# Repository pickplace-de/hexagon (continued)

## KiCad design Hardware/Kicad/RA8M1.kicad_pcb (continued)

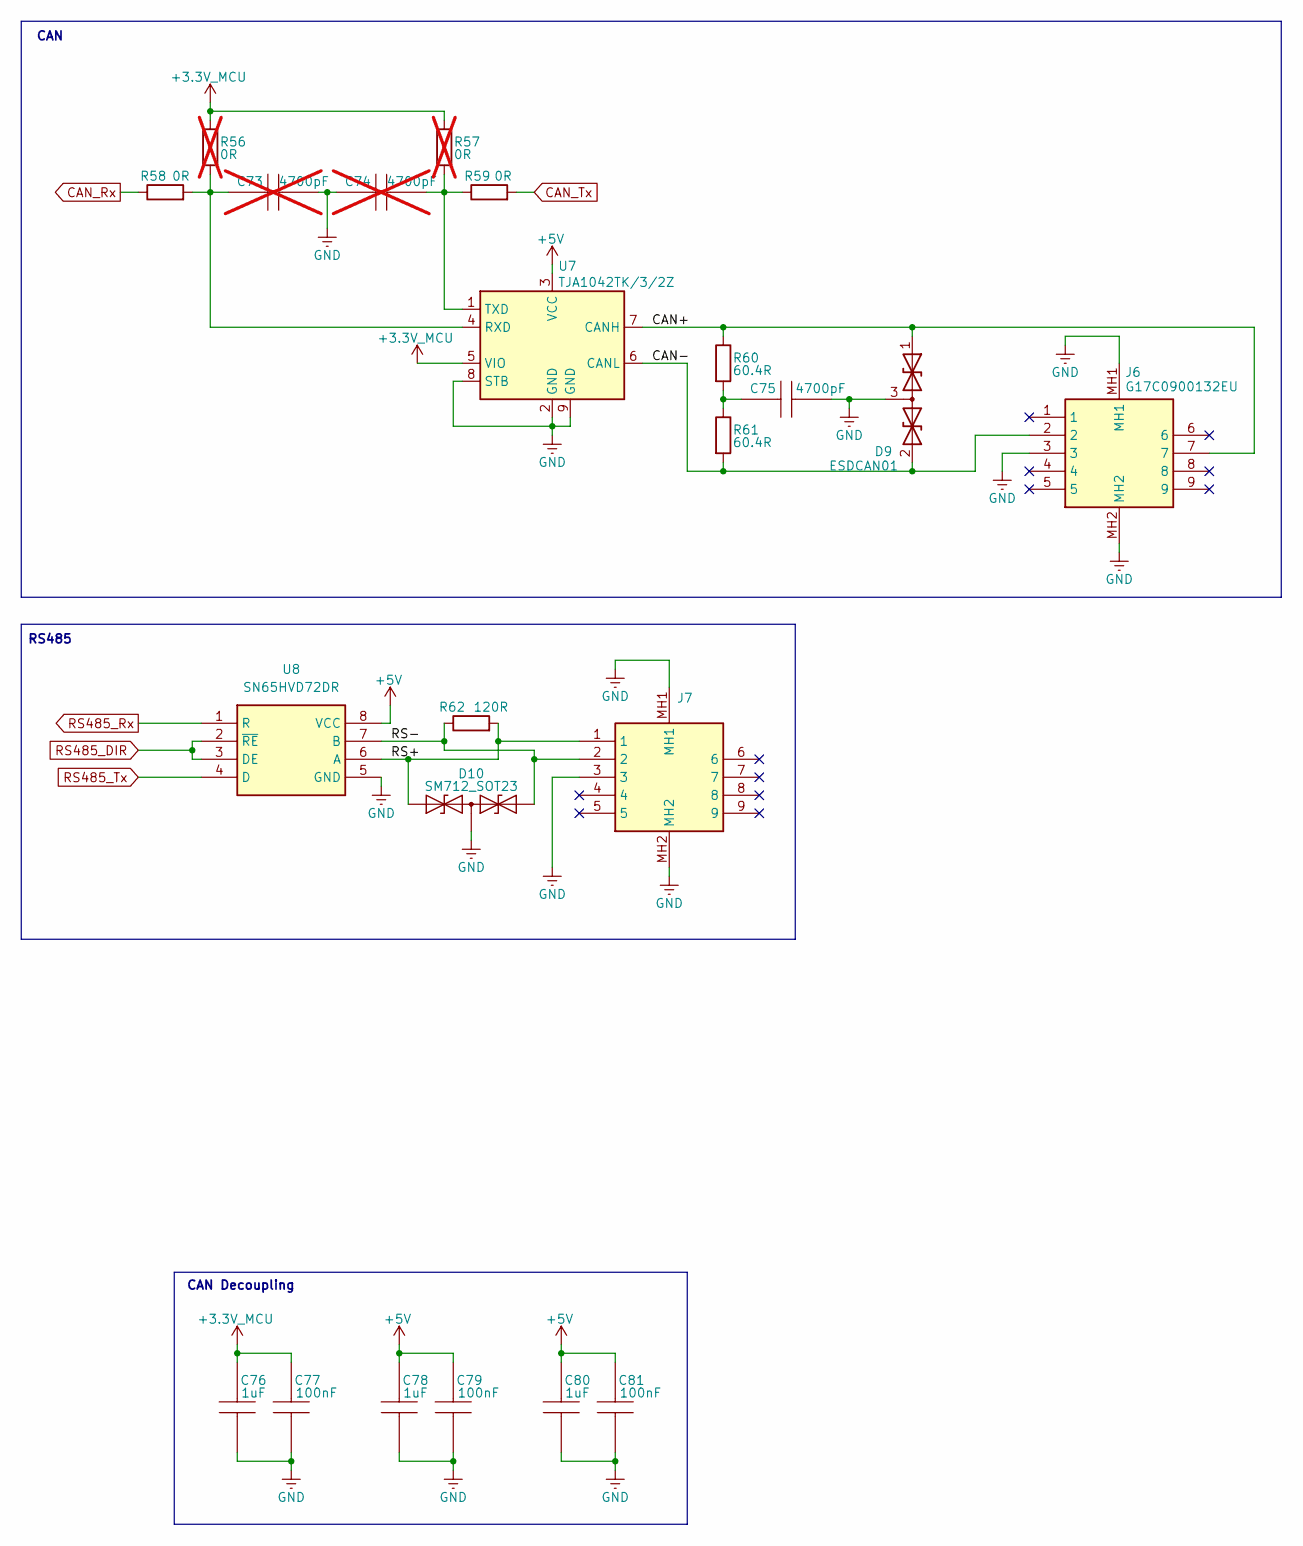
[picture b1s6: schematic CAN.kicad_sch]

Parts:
C73, C74: 4700pF; C_0603_1608Metric; MPN 885012104008; not fitted
C75: 4700pF; C_0603_1608Metric; MPN 885012104008
C76, C78, C80: 1uF; C_0402_1005Metric; MPN 885012105006
C77, C79, C81: 100nF; C_0402_1005Metric; MPN 885012205092
D9: ESDCAN01; TSOT-23
D10: SM712_SOT23; SOT-23
J6, J7: G17C0900132EU; Mouser Part Number 523-G17C0900132EU
R56, R57: 0R; R_0402_1005Metric; MPN 560112110001; not fitted
R58, R59: 0R; R_0402_1005Metric; MPN 560112110001
R60, R61: 60.4R; R_0402_1005Metric; MPN 560112110170
R62: 120R; R_0402_1005Metric; MPN 560112110001
U7: TJA1042TK/3/2Z; DFN-8-1EP_3x3mm_P0.65mm_EP1.55x2.4mm; MPN TJA1042TK/3/2Z
U8: SN65HVD72DR; SOIC127P600X175-8N; Mouser Part Number 595-SN65HVD72DR

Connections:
+3.3V_MCU: C76.2, C77.2, R56.1, R57.1, U7.5 (VIO); also elsewhere on the board
+5V: C78.2, C79.2, C80.2, C81.2, U7.3 (VCC), U8.8 (VCC); also elsewhere on the board
/CAN & RS485/CAN+: D9.1 (A1), J6.7, R60.1, U7.7 (CANH)
/CAN & RS485/CAN-: D9.2 (A2), J6.2, R61.2, U7.6 (CANL)
/CAN & RS485/RS+: D10.1 (A1), J7.1, R62.2, U8.6 (A)
/CAN & RS485/RS-: D10.2 (A2), J7.2, R62.1, U8.7 (B)
CAN_Rx: R58.1; also elsewhere on the board
CAN_Tx: R59.2; also elsewhere on the board
GND: C73.1, C74.2, C75.1, C76.1, C77.1, C78.1, C79.1, C80.1, C81.1, D9.3 (common), D10.3 (common), J6.3, J6.MH1, J6.MH2, J7.3, J7.MH1, J7.MH2, U7.2 (GND), U7.8 (STB), U7.9 (GND), U8.5 (GND); also elsewhere on the board
unnamed: C75.2, R60.2, R61.1
unnamed: C73.2, R56.2, R58.2, U7.4 (RXD)
unnamed: C74.1, R57.2, R59.1, U7.1 (TXD)
RS485_DIR: U8.2 (~RE), U8.3 (DE); also elsewhere on the board
RS485_Rx: U8.1 (R); also elsewhere on the board
RS485_Tx: U8.4 (D); also elsewhere on the board

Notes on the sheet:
CAN Decoupling
CAN
RS485

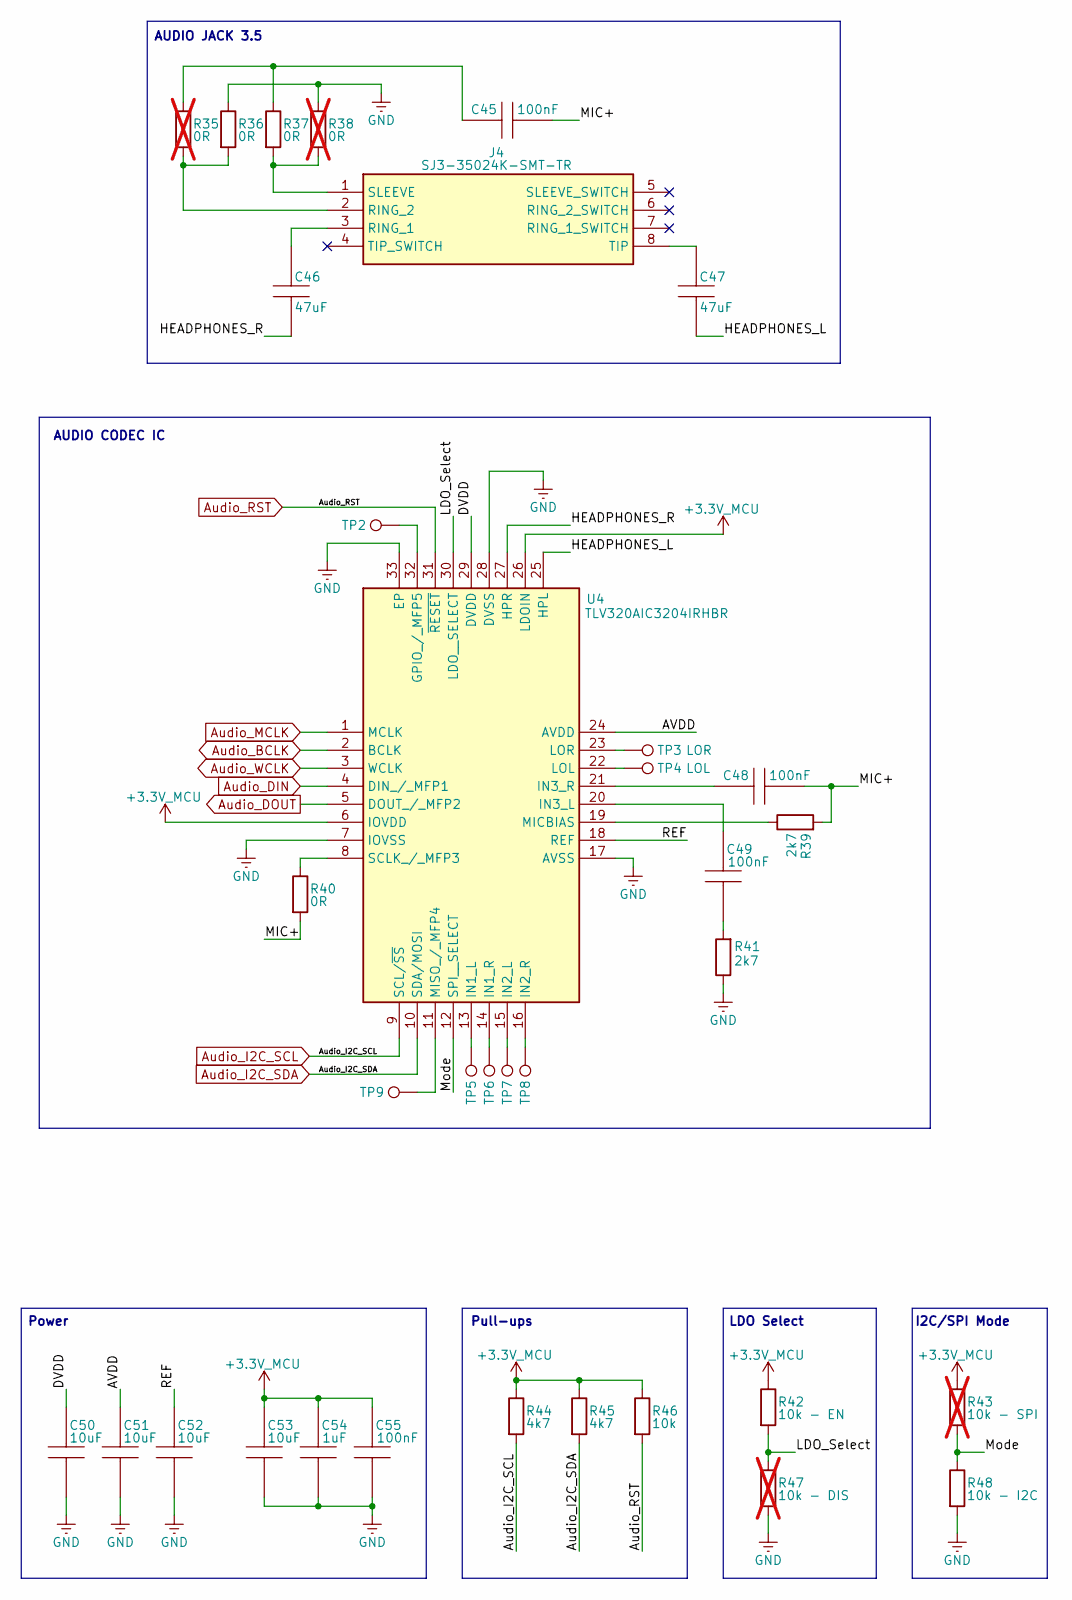
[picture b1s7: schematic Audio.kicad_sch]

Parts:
C45, C48, C49, C55: 100nF; C_0402_1005Metric; MPN 885012205092
C46, C47: 47uF; C_0805_2012Metric; MPN 885012107006
C50, C51, C52, C53: 10uF; C_0402_1005Metric; MPN 885012105020
C54: 1uF; C_0402_1005Metric; MPN 885012105006
J4: SJ3-35024K-SMT-TR; SJ335024KSMTTR; Mouser Part Number 179-SJ3-35024K-SMTTR
R35, R38: 0R; R_0402_1005Metric; MPN 560112110001; not fitted
R36, R37, R40: 0R; R_0402_1005Metric; MPN 560112110001
R39, R41: 2k7; R_0402_1005Metric; MPN 560112110266
R42: 10k - EN; R_0402_1005Metric; MPN 560112110020
R43: 10k - SPI; R_0402_1005Metric; MPN 560112110020; not fitted
R44, R45: 4k7; R_0402_1005Metric; MPN 560112110245
R46: 10k; R_0402_1005Metric; MPN 560112110020
R47: 10k - DIS; R_0402_1005Metric; MPN 560112110020; not fitted
R48: 10k - I2C; R_0402_1005Metric; MPN 560112110020
TP2, TP5, TP6, TP7, TP8, TP9: TestPoint_0.5mm
TP3: LOR; TestPoint_0.5mm
TP4: LOL; TestPoint_0.5mm
U4: TLV320AIC3204IRHBR; QFN50P500X500X100-33N-D; Mouser Part Number 595-V320AIC3204IRHBR

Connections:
+3.3V_MCU: C53.2, C54.2, C55.2, R42.1, R43.1, R44.1, R45.1, R46.1, U4.6 (IOVDD), U4.26 (LDOIN); also elsewhere on the board
/Audio/AVDD: C51.2, U4.24 (AVDD)
/Audio/DVDD: C50.2, U4.29 (DVDD)
/Audio/HEADPHONES_L: C47.2, U4.25 (HPL)
/Audio/HEADPHONES_R: C46.2, U4.27 (HPR)
/Audio/LDO_Select: R42.2, R47.1, U4.30 (LDO__SELECT)
/Audio/MIC+: C45.1, C48.1, R39.2, R40.2
/Audio/Mode: R43.2, R48.1, U4.12 (SPI__SELECT)
/Audio/REF: C52.2, U4.18 (REF)
Audio_BCLK: U4.2 (BCLK); also elsewhere on the board
Audio_DIN: U4.4 (DIN_/_MFP1); also elsewhere on the board
Audio_DOUT: U4.5 (DOUT_/_MFP2); also elsewhere on the board
Audio_I2C_SCL: R44.2, U4.9 (SCL/~SS); also elsewhere on the board
Audio_I2C_SDA: R45.2, U4.10 (SDA/MOSI); also elsewhere on the board
Audio_MCLK: U4.1 (MCLK); also elsewhere on the board
Audio_RST: R46.2, U4.31 (~RESET); also elsewhere on the board
Audio_WCLK: U4.3 (WCLK); also elsewhere on the board
GND: C50.1, C51.1, C52.1, C53.1, C54.1, C55.1, R36.1, R38.1, R41.1, R47.2, R48.2, U4.7 (IOVSS), U4.17 (AVSS), U4.28 (DVSS), U4.33 (EP); also elsewhere on the board
unnamed: C45.2, R35.1, R37.1
unnamed: C49.1, R41.2
unnamed: C46.1, J4.3 (RING_1)
unnamed: J4.2 (RING_2), R35.2, R36.2
unnamed: J4.1 (SLEEVE), R37.2, R38.2
unnamed: C47.1, J4.8 (TIP)
unnamed: TP2.1, U4.32 (GPIO_/_MFP5)
unnamed: TP5.1, U4.13 (IN1_L)
unnamed: TP6.1, U4.14 (IN1_R)
unnamed: TP7.1, U4.15 (IN2_L)
unnamed: TP8.1, U4.16 (IN2_R)
unnamed: C49.2, U4.20 (IN3_L)
unnamed: C48.2, U4.21 (IN3_R)
unnamed: TP4.1, U4.22 (LOL)
unnamed: TP3.1, U4.23 (LOR)
unnamed: R39.1, U4.19 (MICBIAS)
unnamed: TP9.1, U4.11 (MISO_/_MFP4)
unnamed: R40.1, U4.8 (SCLK_/_MFP3)

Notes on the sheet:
LDO Select
AUDIO JACK 3.5
AUDIO CODEC IC
Power
I2C/SPI Mode
Pull-ups

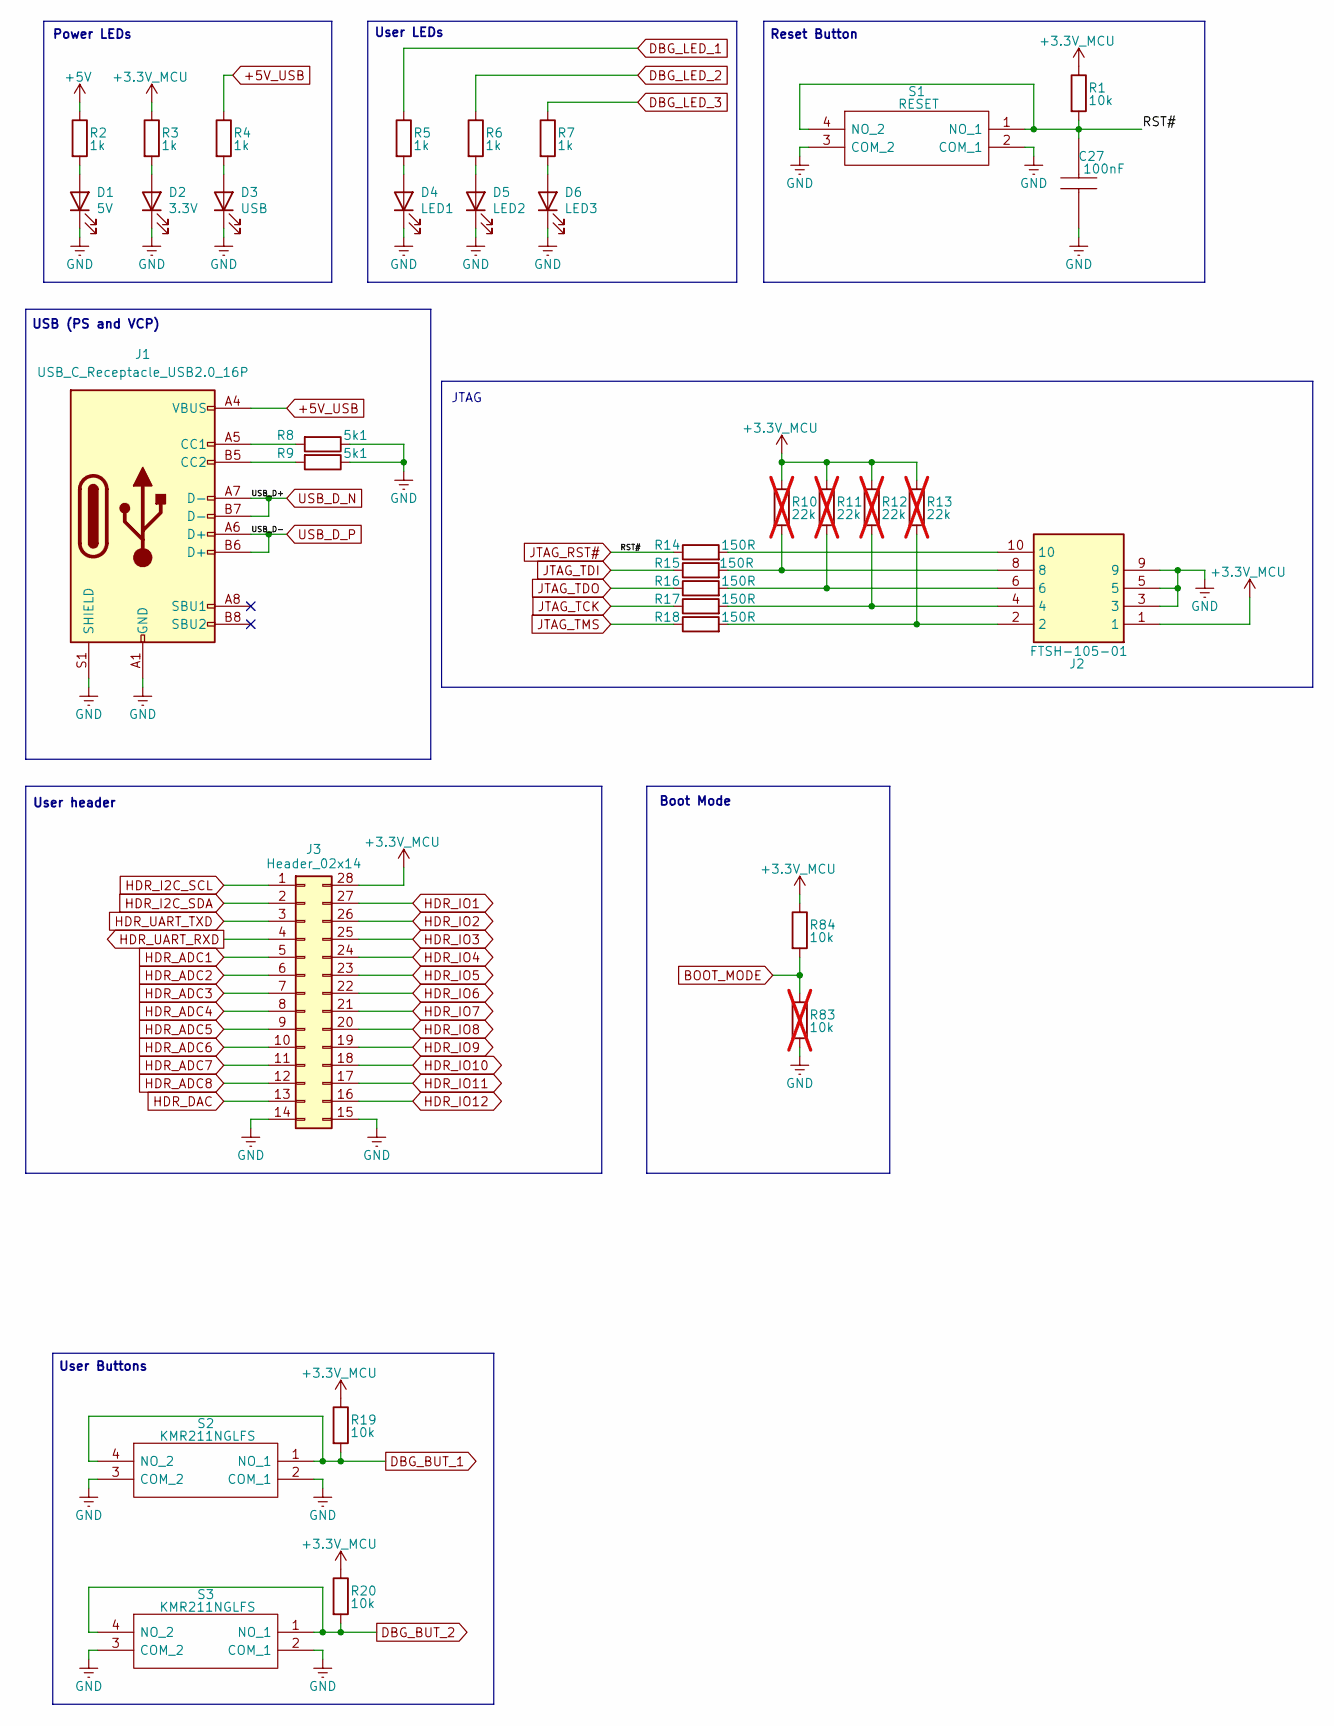
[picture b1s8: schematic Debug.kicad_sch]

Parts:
C27: 100nF; C_0402_1005Metric; MPN 885012205092
D1: 5V; LED_0805_2012Metric; MPN 150080RS75000
D2: 3.3V; LED_0805_2012Metric; MPN 150080RS75000
D3: USB; LED_0805_2012Metric; MPN 150080RS75000
D4: LED1; LED_0805_2012Metric; MPN 150080RS75000
D5: LED2; LED_0805_2012Metric; MPN 150080RS75000
D6: LED3; LED_0805_2012Metric; MPN 150080RS75000
J1: USB_C_Receptacle_USB2.0_16P; USB_C_Receptacle_GCT_USB4110; MPN USB4110-GF-A
J2: FTSH-105-01; FTSH10501LDV007K; Mouser Part Number 200-FTSH10501LDV7KP
J3: Header_02x14; PinHeader_2x14_P2.54mm_Vertical
R1, R19, R20, R84: 10k; R_0402_1005Metric; MPN 560112110020
R2, R3, R4, R5, R6, R7: 1k; R_0402_1005Metric; MPN 560112110012
R8, R9: 5k1; R_0402_1005Metric; MPN 560112120019
R10, R11, R12, R13: 22k; R_0402_1005Metric; MPN 560112110098; not fitted
R14, R15, R16, R17, R18: 150R; R_0402_1005Metric; MPN 560112110061
R83: 10k; R_0402_1005Metric; MPN 560112110020; not fitted
S1: RESET; KMR211NGLFS-1; Mouser Part Number 611-KMR211NGLFS
S2, S3: KMR211NGLFS; KMR211NGLFS-1; Mouser Part Number 611-KMR211NGLFS

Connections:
+3.3V_MCU: J2.1, J3.28, R1.1, R3.1, R10.1, R11.1, R12.1, R13.1, R19.1, R20.1, R84.1; also elsewhere on the board
+5V: R2.1; also elsewhere on the board
+5V_USB: J1.A4 (VBUS), J1.A9 (VBUS), J1.B4 (VBUS), J1.B9 (VBUS), R4.1; also elsewhere on the board
BOOT_MODE: R83.1, R84.2; also elsewhere on the board
DBG_BUT_1: R19.2, S2.1 (NO_1), S2.4 (NO_2); also elsewhere on the board
DBG_BUT_2: R20.2, S3.1 (NO_1), S3.4 (NO_2); also elsewhere on the board
DBG_LED_1: R5.1; also elsewhere on the board
DBG_LED_2: R6.1; also elsewhere on the board
DBG_LED_3: R7.1; also elsewhere on the board
GND: C27.1, D1.1 (K), D2.1 (K), D3.1 (K), D4.1 (K), D5.1 (K), D6.1 (K), J1.A1 (GND), J1.A12 (GND), J1.B1 (GND), J1.B12 (GND), J1.S1 (SHIELD), J2.3, J2.5, J2.9, J3.14, J3.15, R8.1, R9.1, R83.2, S1.2 (COM_1), S1.3 (COM_2), S2.2 (COM_1), S2.3 (COM_2), S3.2 (COM_1), S3.3 (COM_2); also elsewhere on the board
HDR_ADC1: J3.5; also elsewhere on the board
HDR_ADC2: J3.6; also elsewhere on the board
HDR_ADC3: J3.7; also elsewhere on the board
HDR_ADC4: J3.8; also elsewhere on the board
HDR_ADC5: J3.9; also elsewhere on the board
HDR_ADC6: J3.10; also elsewhere on the board
HDR_ADC7: J3.11; also elsewhere on the board
HDR_ADC8: J3.12; also elsewhere on the board
HDR_DAC: J3.13; also elsewhere on the board
HDR_I2C_SCL: J3.1; also elsewhere on the board
HDR_I2C_SDA: J3.2; also elsewhere on the board
HDR_IO1: J3.27; also elsewhere on the board
HDR_IO2: J3.26; also elsewhere on the board
HDR_IO3: J3.25; also elsewhere on the board
HDR_IO4: J3.24; also elsewhere on the board
HDR_IO5: J3.23; also elsewhere on the board
HDR_IO6: J3.22; also elsewhere on the board
HDR_IO7: J3.21; also elsewhere on the board
HDR_IO8: J3.20; also elsewhere on the board
HDR_IO9: J3.19; also elsewhere on the board
HDR_IO10: J3.18; also elsewhere on the board
HDR_IO11: J3.17; also elsewhere on the board
HDR_IO12: J3.16; also elsewhere on the board
HDR_UART_RXD: J3.4; also elsewhere on the board
HDR_UART_TXD: J3.3; also elsewhere on the board
JTAG_RST#: C27.2, R1.2, R14.1, S1.1 (NO_1), S1.4 (NO_2); also elsewhere on the board
JTAG_TCK: R17.1; also elsewhere on the board
JTAG_TDI: R15.1; also elsewhere on the board
JTAG_TDO: R16.1; also elsewhere on the board
JTAG_TMS: R18.1; also elsewhere on the board
unnamed: D1.2 (A), R2.2
unnamed: D2.2 (A), R3.2
unnamed: D3.2 (A), R4.2
unnamed: D4.2 (A), R5.2
unnamed: D5.2 (A), R6.2
unnamed: D6.2 (A), R7.2
unnamed: J1.A5 (CC1), R8.2
unnamed: J1.B5 (CC2), R9.2
unnamed: J2.2, R13.2, R18.2
unnamed: J2.4, R12.2, R17.2
unnamed: J2.6, R11.2, R16.2
unnamed: J2.8, R10.2, R15.2
unnamed: J2.10, R14.2
USB_D_N: J1.A7 (D-), J1.B7 (D-); also elsewhere on the board
USB_D_P: J1.A6 (D+), J1.B6 (D+); also elsewhere on the board

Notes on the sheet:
User header
User Buttons
Power LEDs
User LEDs
USB (PS and VCP)
JTAG
Reset Button
Boot Mode

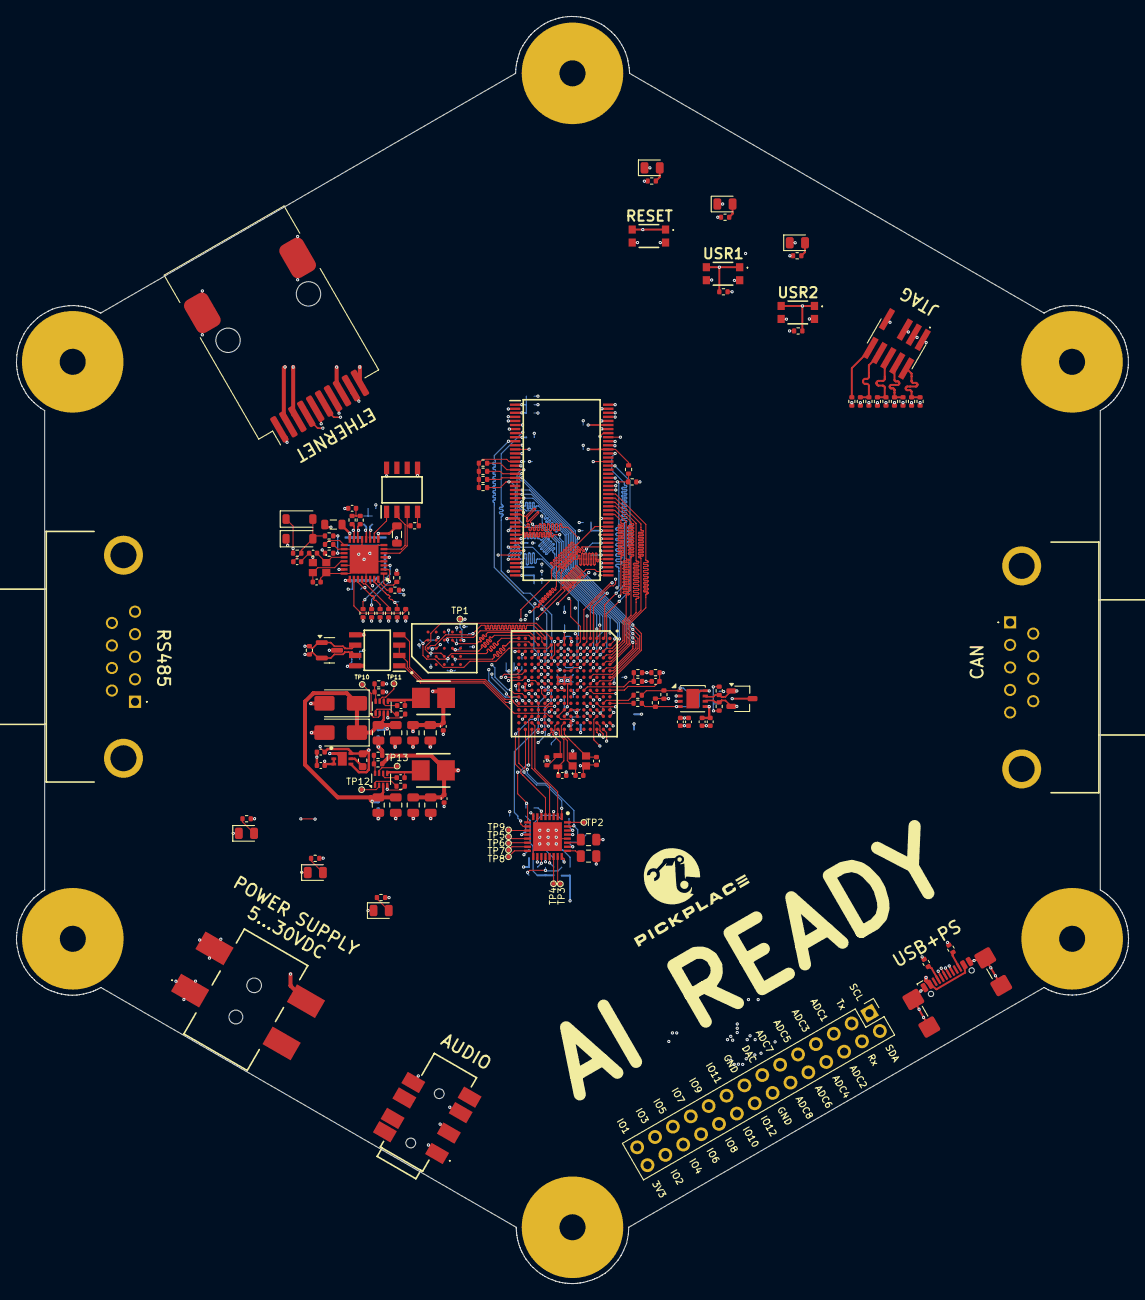
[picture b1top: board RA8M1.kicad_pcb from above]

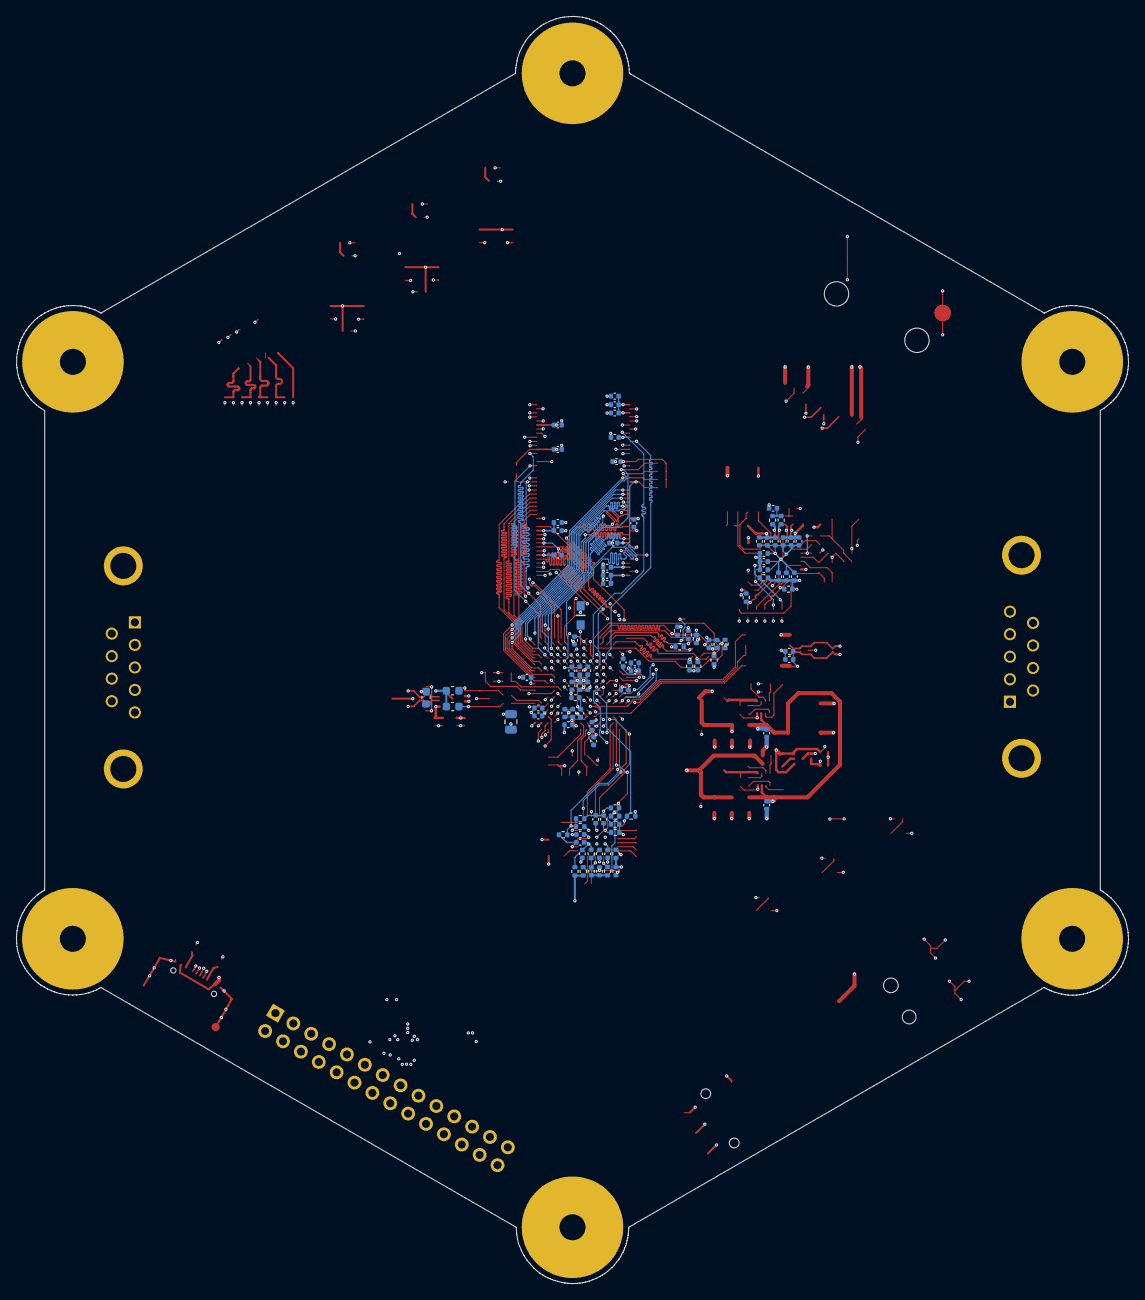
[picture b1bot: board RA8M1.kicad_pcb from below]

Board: 8 copper layers, 136.9 x 155.9 mm, 236 parts (96 on the bottom side), 221 nets.

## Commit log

2025-04-19 gitignore added and a small clean-up
2025-05-13 Ground planes fix
2025-05-26 cosmetic fix
